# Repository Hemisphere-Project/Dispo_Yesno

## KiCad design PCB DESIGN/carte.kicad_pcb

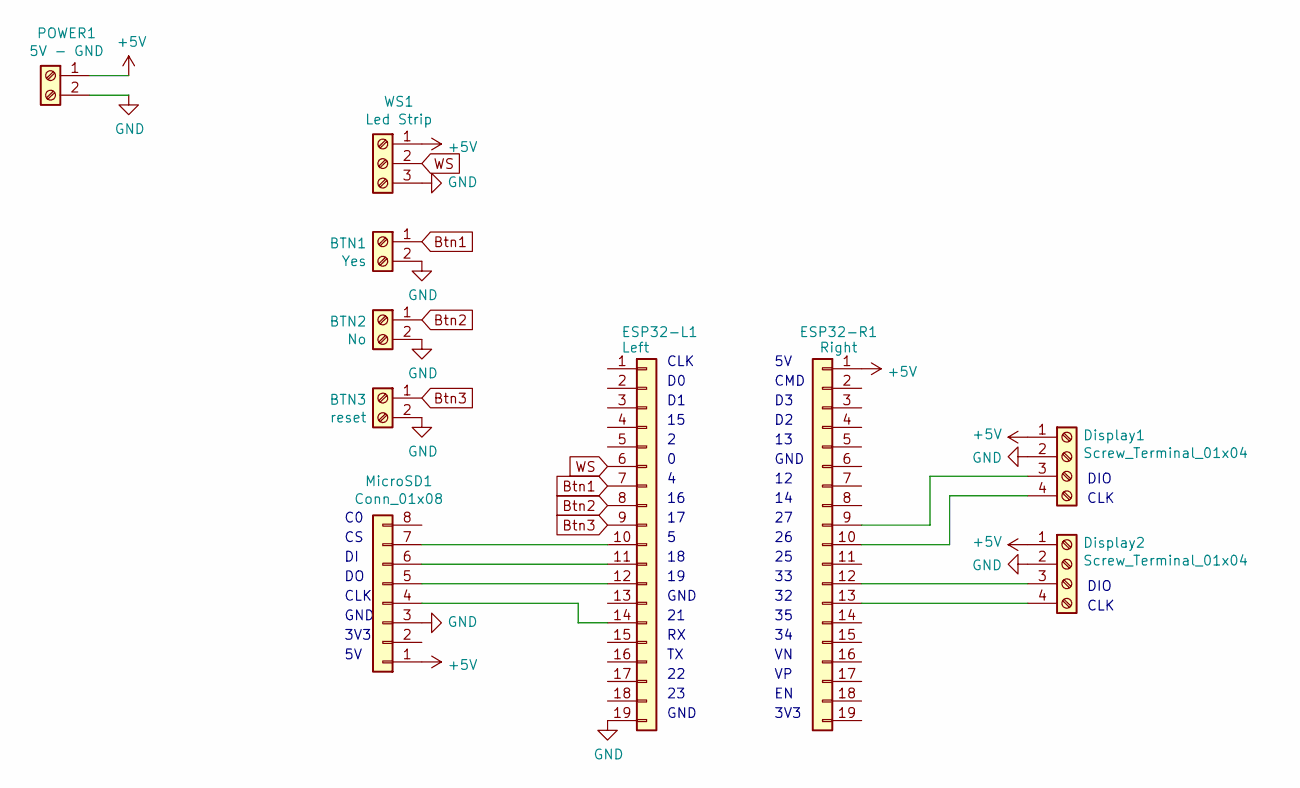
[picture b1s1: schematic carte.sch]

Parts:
BTN1: Yes; TerminalBlock_bornier-2_P5.08mm
BTN2: No; TerminalBlock_bornier-2_P5.08mm
BTN3: reset; TerminalBlock_bornier-2_P5.08mm
Display1, Display2: Screw_Terminal_01x04; TerminalBlock_bornier-4_P5.08mm
ESP32-L1: Left; PinSocket_1x19_P2.54mm_Vertical
ESP32-R1: Right; PinSocket_1x19_P2.54mm_Vertical
MicroSD1: Conn_01x08; PinSocket_1x08_P2.54mm_Vertical
POWER1: 5V - GND; TerminalBlock_bornier-2_P5.08mm
WS1: Led Strip; TerminalBlock_bornier-3_P5.08mm

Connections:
+5V: Display1.1, Display2.1, ESP32-R1.1, MicroSD1.1, POWER1.1, WS1.1
Btn1: BTN1.1, ESP32-L1.7
Btn2: BTN2.1, ESP32-L1.8
Btn3: BTN3.1, ESP32-L1.9
GND: BTN1.2, BTN2.2, BTN3.2, Display1.2, Display2.2, ESP32-L1.19, MicroSD1.3, POWER1.2, WS1.3
unnamed: Display1.3, ESP32-R1.9
unnamed: Display1.4, ESP32-R1.10
unnamed: Display2.3, ESP32-R1.12
unnamed: Display2.4, ESP32-R1.13
unnamed: ESP32-L1.10, MicroSD1.7
unnamed: ESP32-L1.11, MicroSD1.6
unnamed: ESP32-L1.12, MicroSD1.5
unnamed: ESP32-L1.14, MicroSD1.4
WS: ESP32-L1.6, WS1.2

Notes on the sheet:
CLK
GND
CMD
3V3
DIO

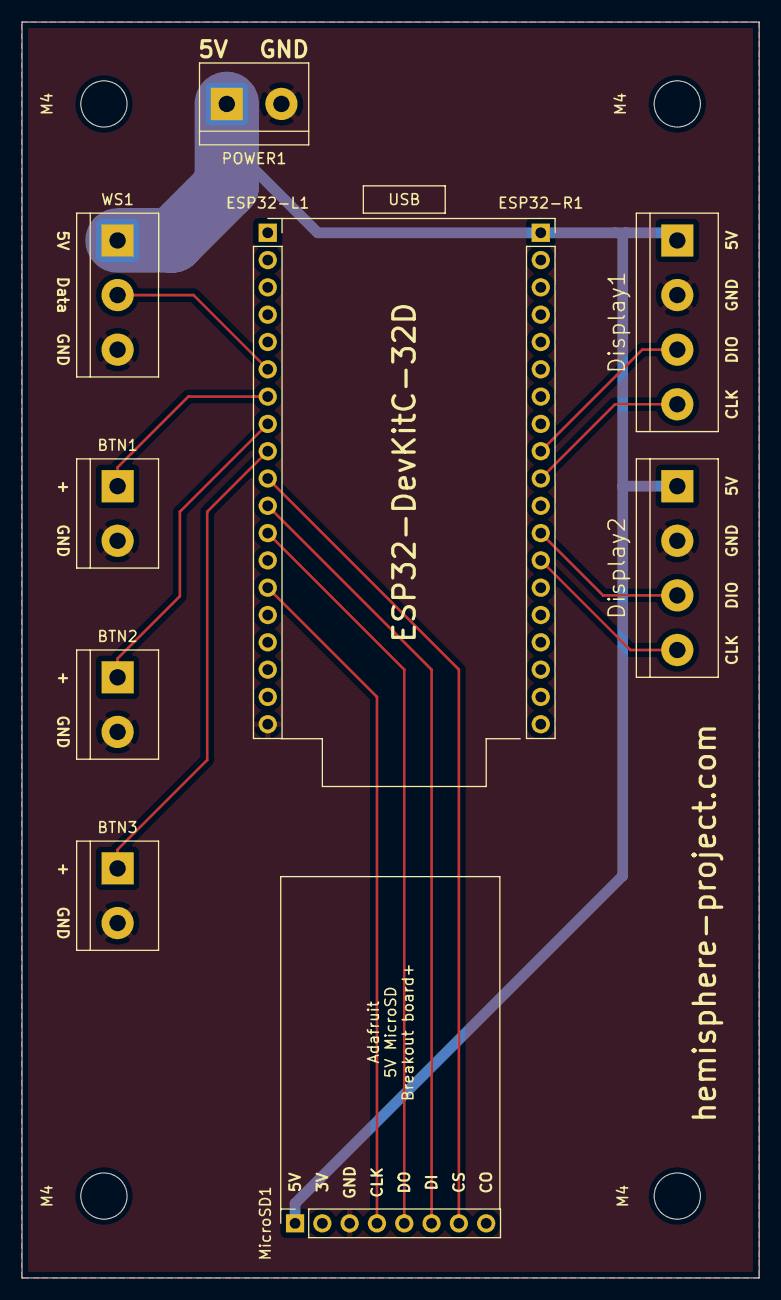
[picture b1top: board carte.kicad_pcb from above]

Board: 2 copper layers, 68.6 x 116.8 mm, 14 parts (0 on the bottom side), 14 nets.

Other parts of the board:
M4, M4#2, M4#3, M4#4: MountingHole_4.3mm_M4

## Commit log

2019-06-26 init
2019-07-02 TM1637 ok
2019-07-03 TM1637 clean
2019-07-03 tm1637 included
2019-07-03 start anim
2019-07-08 show
2019-07-09 oscillation added
2019-07-09 1 sec
2019-07-09 fix?
2019-07-10 delay big chiffres
2019-07-10 nikel
2019-07-11 modifs réu timing ok
2019-09-12 CV files update
2019-09-12 anim While Reset
2019-09-12 Todo
2019-10-01 Panel id & reverse left right
2019-10-01 Selective roads & mapping offset
2019-10-01 config mode
2019-10-01 roads
2019-10-02 roads ok
2019-10-02 add wifi / ota / debug
2019-10-02 ota & wifi
2019-10-02 ready
2019-10-09 red white
